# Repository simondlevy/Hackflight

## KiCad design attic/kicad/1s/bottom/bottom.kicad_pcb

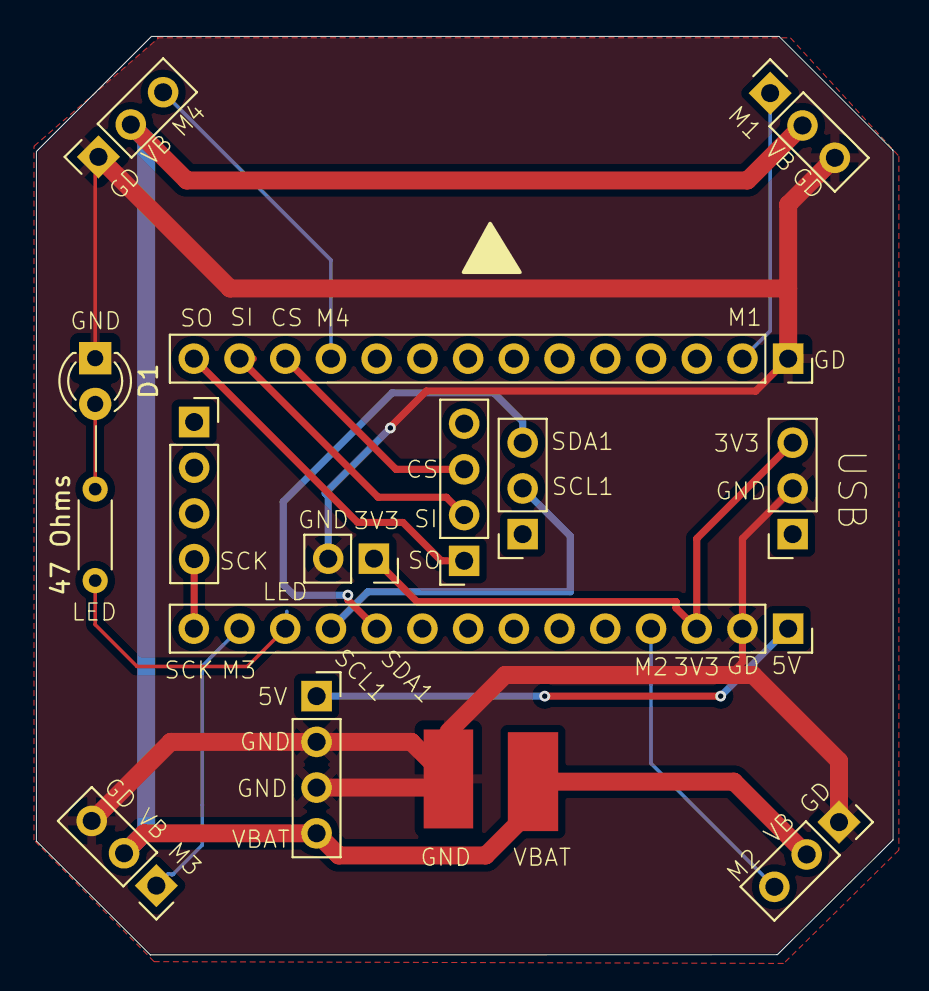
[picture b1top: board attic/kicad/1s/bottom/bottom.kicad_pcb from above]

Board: 2 copper layers, 47.6 x 51.0 mm, 16 parts (0 on the bottom side), 16 nets.

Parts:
D1: LED; LED_D3.0mm
GND_PAD1: Conn_01x01; SolderWirePad_1x01_SMD_5x10mm
J1, J6, J8: Conn_01x04_Socket; PinSocket_1x04_P2.54mm_Vertical
J2, J7: Conn_01x03_Socket; PinSocket_1x03_P2.54mm_Vertical
J3: Conn_01x02_Socket; PinSocket_1x02_P2.54mm_Vertical
J4, J5: Conn_01x14_Socket; PinSocket_1x14_P2.54mm_Vertical
M1, M2, M3, M4: Conn_01x03_Socket; PinSocket_1x03_P2.54mm_Vertical
R1: 47 Ohms; R_Axial_DIN0204_L3.6mm_D1.6mm_P5.08mm_Horizontal
VB_PAD1: Conn_01x01; SolderWirePad_1x01_SMD_5x10mm

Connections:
/3V3: J2.3, J3.1, J4.3
/5V: J4.1, J8.1
/CS: J5.12, J6.3
/GND: D1.1 (K), GND_PAD1.1, J2.2, J3.2, J4.2, J5.1, J8.2, J8.3, M1.3, M2.1, M3.3, M4.1
/LED1: J4.12, R1.2
/M1: J5.2, M1.1
/M2: J4.4, M2.3
/M3: J4.13, M3.1
/M4: J5.11, M4.3
/MISO: J5.14, J6.1
/MOSI: J5.13, J6.2
/SCK: J1.4, J4.14
/SCL1: J4.11, J7.2
/SDA1: J4.10, J7.3
/VBAT: J8.4, M1.2, M2.2, M3.2, M4.2, VB_PAD1.1
unnamed: D1.2 (A), R1.1

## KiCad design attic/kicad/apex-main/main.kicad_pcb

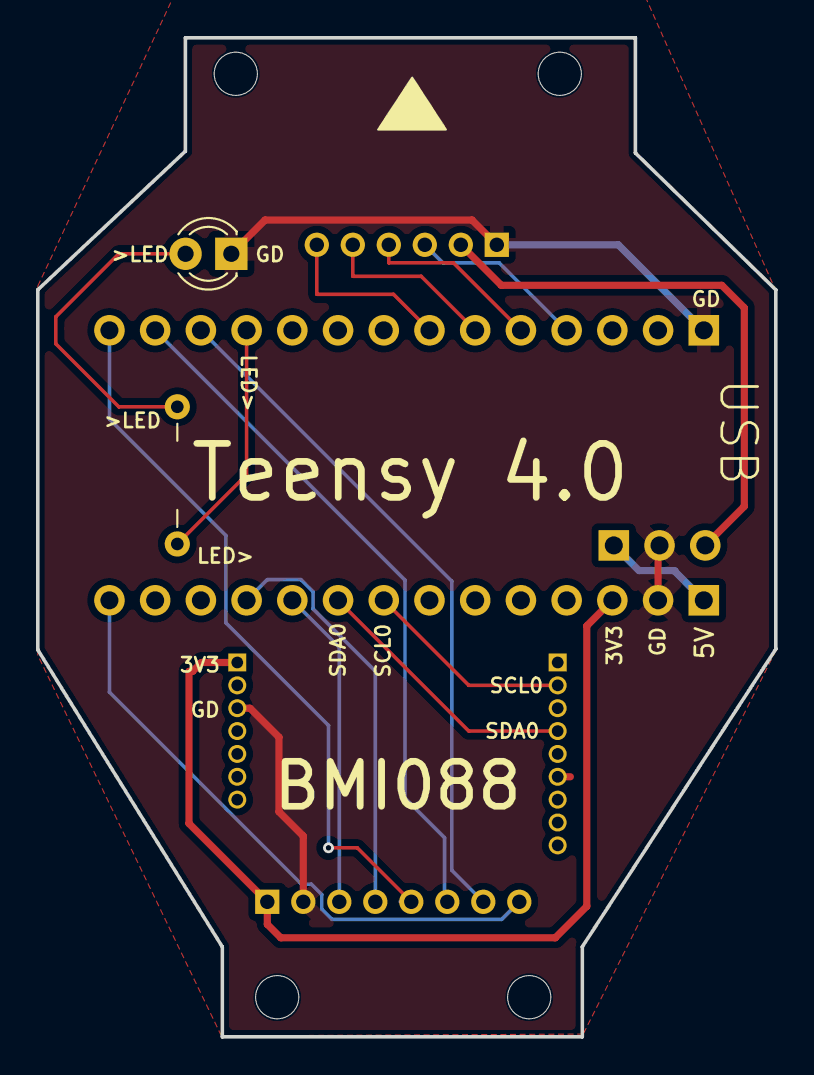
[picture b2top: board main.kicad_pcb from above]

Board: 2 copper layers, 41.0 x 55.5 mm, 16 parts (0 on the bottom side), 18 nets.

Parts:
D1: LED; LED_D3.0mm_FlatTop
H1, H1#2, H1#3, H1#4, H2, H3, H4: MountingHole; MountingHole_2.1mm
J1: Conn_01x14; PinSocket_1x14_P2.54mm_Vertical
J2: Conn_01x14_Socket; PinSocket_1x14_P2.54mm_Vertical
J4: Conn_01x03_Socket; PinHeader_1x03_P2.54mm_Vertical
J5: Conn_01x06; PinSocket_1x06_P2.00mm_Vertical
J6: Conn_01x08; PinSocket_1x08_P2.00mm_Vertical
J7: Conn_01x07; PinHeader_1x07_P1.27mm_Vertical
J8: Conn_01x09; PinHeader_1x09_P1.27mm_Vertical
R1: R; R_Axial_DIN0204_L3.6mm_D1.6mm_P7.62mm_Horizontal

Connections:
/3V3: J2.3, J6.1, J7.1
/5V: J2.1, J4.1
/CS: J1.12, J6.7
/GND: D1.1 (K), J1.1, J2.2, J4.2, J5.1, J6.2, J7.3
/LED: J1.11, R1.2
/M1: J1.4, J5.3
/M2: J1.5, J5.4
/M3: J1.6, J5.5
/M4: J1.7, J5.6
/MISO: J1.14, J6.5
/MOSI: J1.13, J6.6
/SCK: J2.14, J6.8
/SCL0: J2.8, J8.2
/SCL1: J2.11, J6.4
/SDA0: J2.9, J8.4
/SDA1: J2.10, J6.3
/VBAT: J4.3, J5.2
unnamed: D1.2 (A), R1.1

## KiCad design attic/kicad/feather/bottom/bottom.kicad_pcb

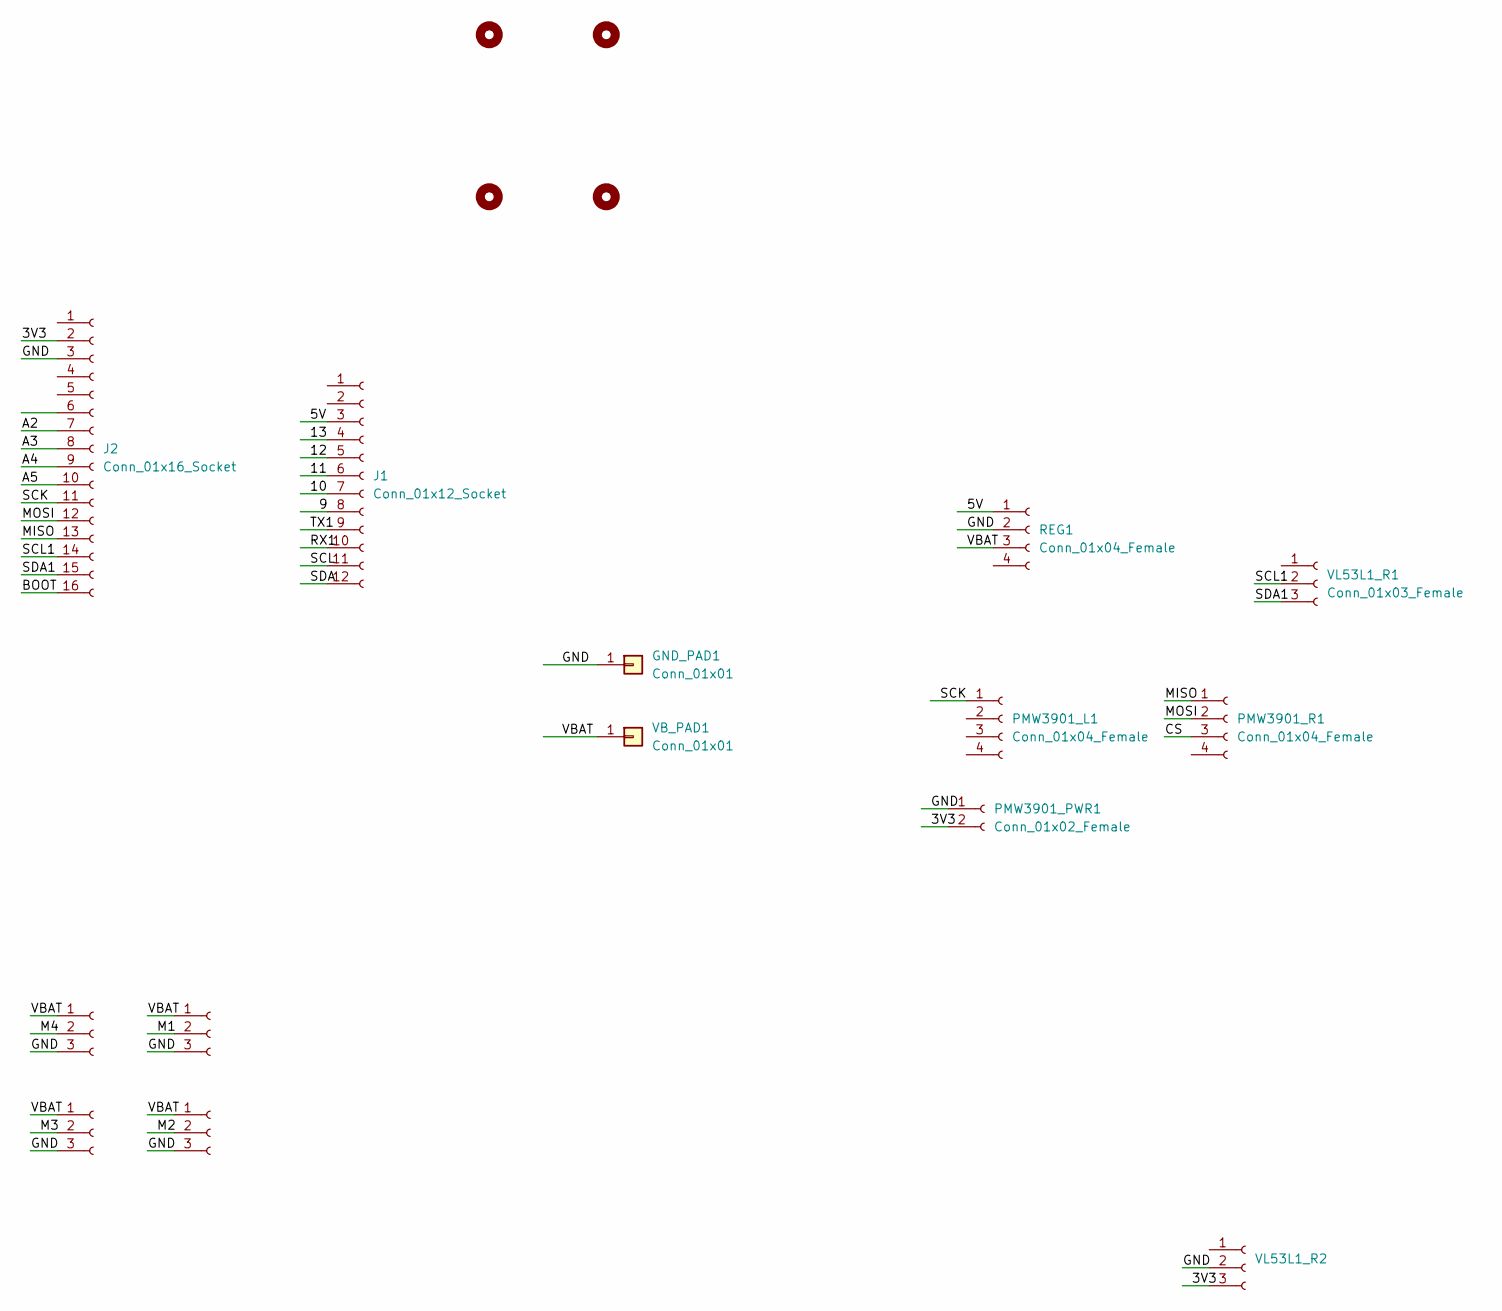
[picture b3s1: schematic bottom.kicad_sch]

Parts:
GND_PAD1: Conn_01x01; SolderWirePad_1x01_SMD_5x10mm
J1: Conn_01x12_Socket; PinSocket_1x14_P2.54mm_Vertical
J2: Conn_01x16_Socket; PinSocket_1x16_P2.54mm_Vertical
M1_GND1: Conn_01x03_Female; PinHeader_1x03_P2.54mm_Vertical
PMW3901_L1, PMW3901_R1: Conn_01x04_Female; PinSocket_1x04_P2.54mm_Vertical
PMW3901_PWR1: Conn_01x02_Female; PinHeader_1x02_P2.54mm_Vertical
POST_1, POST_2, POST_3, POST_4: MountingHole; MountingHole_2.2mm_M2
REG1: Conn_01x04_Female; PinSocket_1x04_P2.54mm_Vertical
VB_PAD1: Conn_01x01; SolderWirePad_1x01_SMD_5x10mm
VL53L1_L3, VL53L1_L4, VL53L1_L5, VL53L1_R1, VL53L1_R2: Conn_01x03_Female; PinHeader_1x03_P2.54mm_Vertical

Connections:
/3V3: J2.2, PMW3901_PWR1.2, VL53L1_R2.3
/5V: J1.3, REG1.1
/9: J1.8
/10: J1.7
/11: J1.6
/12: J1.5
/13: J1.4
/A2: J2.7
/A3: J2.8
/A4: J2.9
/A5: J2.10
/BOOT: J2.16
/CS: PMW3901_R1.3
/GND: GND_PAD1.1, J2.3, M1_GND1.3, PMW3901_PWR1.1, REG1.2, VL53L1_L3.3, VL53L1_L4.3, VL53L1_L5.3, VL53L1_R2.2
/M1: M1_GND1.2
/M2: VL53L1_L3.2
/M3: VL53L1_L5.2
/M4: VL53L1_L4.2
/MISO: J2.13, PMW3901_R1.1
/MOSI: J2.12, PMW3901_R1.2
/RX1: J1.10
/SCK: J2.11, PMW3901_L1.1
/SCL: J1.11
/SCL1: J2.14, VL53L1_R1.2
/SDA: J1.12
/SDA1: J2.15, VL53L1_R1.3
/TX1: J1.9
/VBAT: M1_GND1.1, REG1.3, VB_PAD1.1, VL53L1_L3.1, VL53L1_L4.1, VL53L1_L5.1

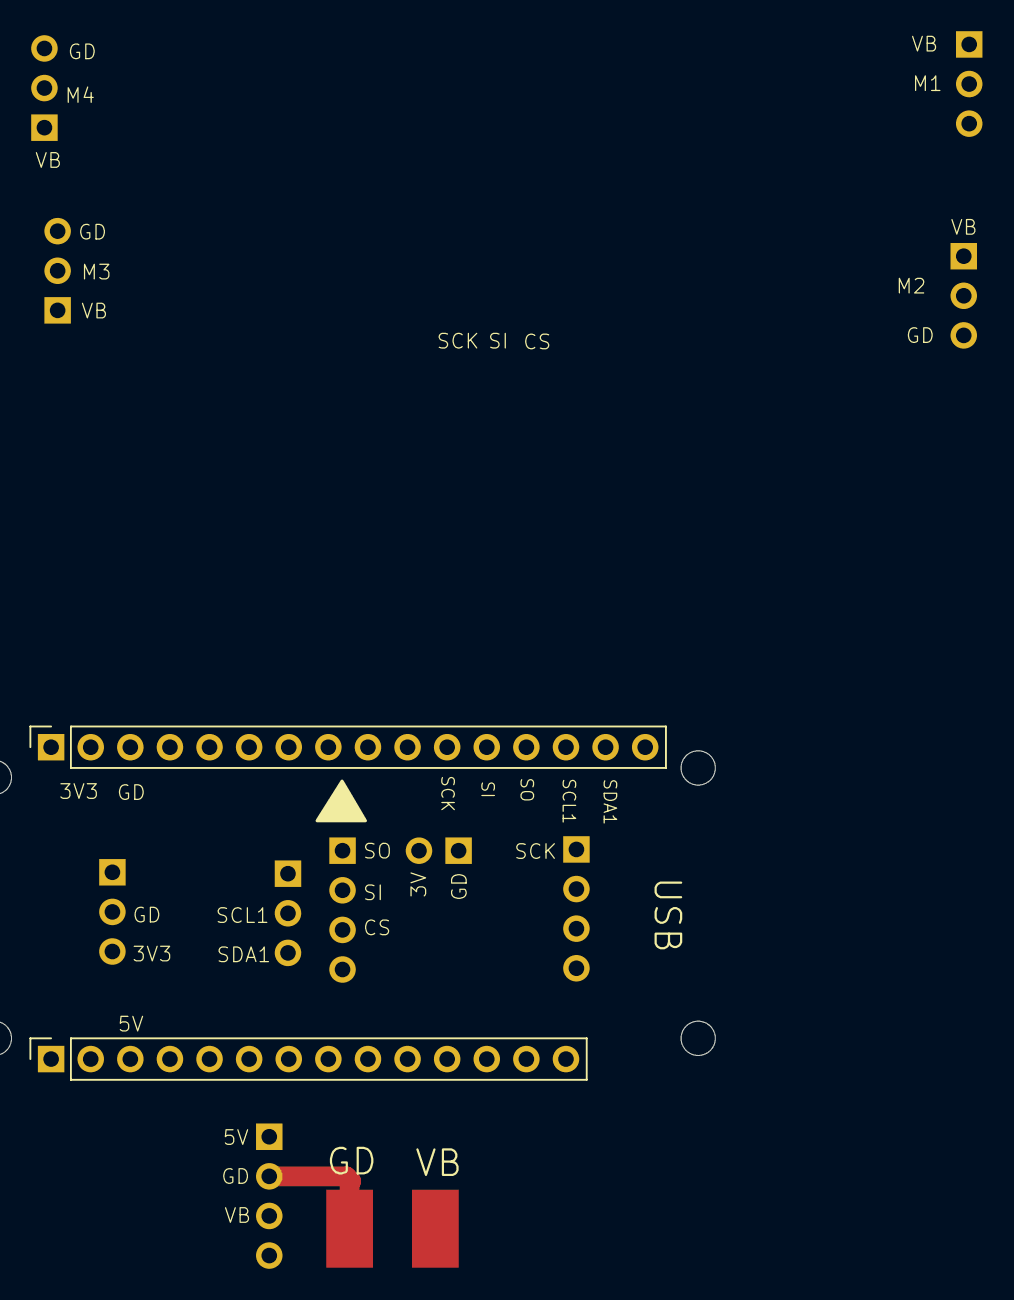
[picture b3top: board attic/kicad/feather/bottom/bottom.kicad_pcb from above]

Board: 2 copper layers, 18 parts (0 on the bottom side), 9 nets.

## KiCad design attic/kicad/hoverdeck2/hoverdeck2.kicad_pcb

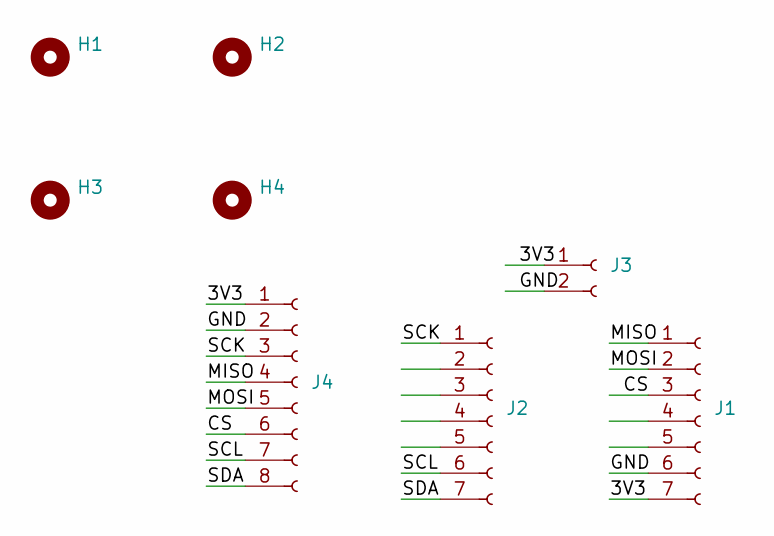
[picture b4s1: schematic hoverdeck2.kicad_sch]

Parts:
H1, H2, H3, H4: MountingHole; MountingHole_2.5mm
J1, J2: Conn_01x07_Socket; PinSocket_1x07_P2.54mm_Vertical
J3: Conn_01x02_Socket; PinSocket_1x02_P2.54mm_Vertical
J4: Conn_01x08_Socket; PinSocket_1x08_P2.00mm_Vertical

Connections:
/3V3: J1.7, J3.1, J4.1
/CS: J1.3, J4.6
/GND: J1.6, J3.2, J4.2
/MISO: J1.1, J4.4
/MOSI: J1.2, J4.5
/SCK: J2.1, J4.3
/SCL: J2.6, J4.7
/SDA: J2.7, J4.8

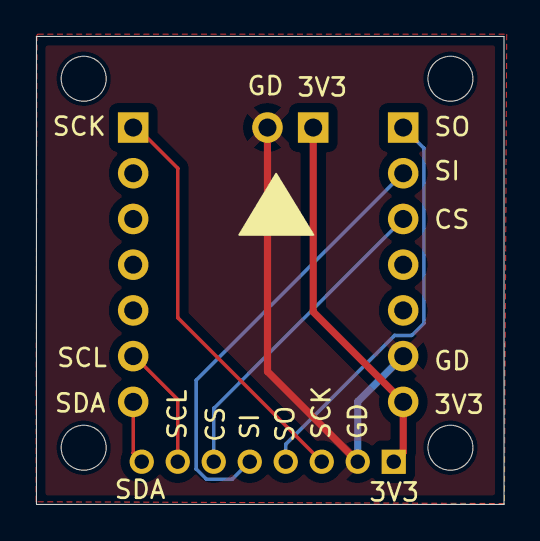
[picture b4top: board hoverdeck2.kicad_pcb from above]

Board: 2 copper layers, 26.0 x 26.0 mm, 8 parts (0 on the bottom side), 8 nets.

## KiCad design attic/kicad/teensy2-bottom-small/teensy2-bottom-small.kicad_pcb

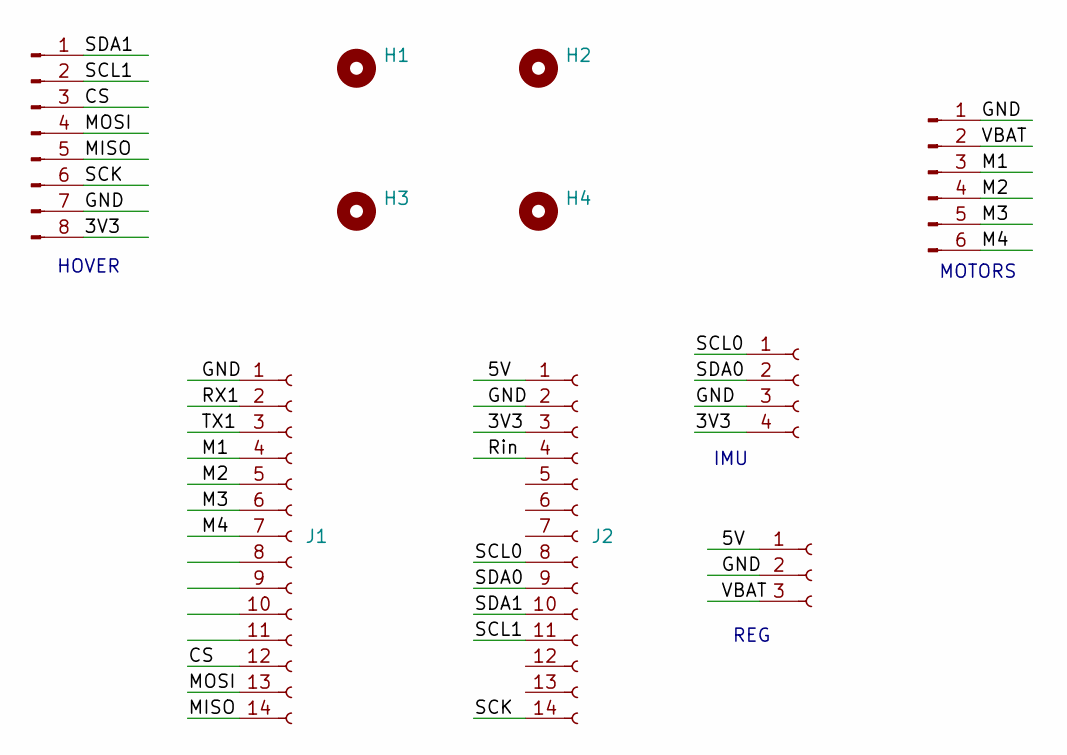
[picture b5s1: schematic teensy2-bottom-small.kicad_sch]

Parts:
H1, H2, H3, H4: MountingHole; MountingHole_2.5mm
J1, J2: Conn_01x14_Socket; PinSocket_1x14_P2.54mm_Vertical
J3: Conn_01x04_Socket; PinHeader_1x04_P2.54mm_Vertical
J4: Conn_01x03_Socket; PinHeader_1x03_P2.54mm_Vertical
J5: Conn_01x06_Pin; PinHeader_1x06_P2.00mm_Vertical
J7: Conn_01x08_Pin; PinSocket_1x08_P2.00mm_Vertical

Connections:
/3V3: J2.3, J3.4, J7.8
/5V: J2.1, J4.1
/CS: J1.12, J7.3
/GND: J1.1, J2.2, J3.3, J4.2, J5.1, J7.7
/M1: J1.4, J5.3
/M2: J1.5, J5.4
/M3: J1.6, J5.5
/M4: J1.7, J5.6
/MISO: J1.14, J7.5
/MOSI: J1.13, J7.4
/RX1: J1.2
/Rin: J2.4
/SCK: J2.14, J7.6
/SCL0: J2.8, J3.1
/SCL1: J2.11, J7.2
/SDA0: J2.9, J3.2
/SDA1: J2.10, J7.1
/TX1: J1.3
/VBAT: J4.3, J5.2

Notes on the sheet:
HOVER
REG
IMU
MOTORS

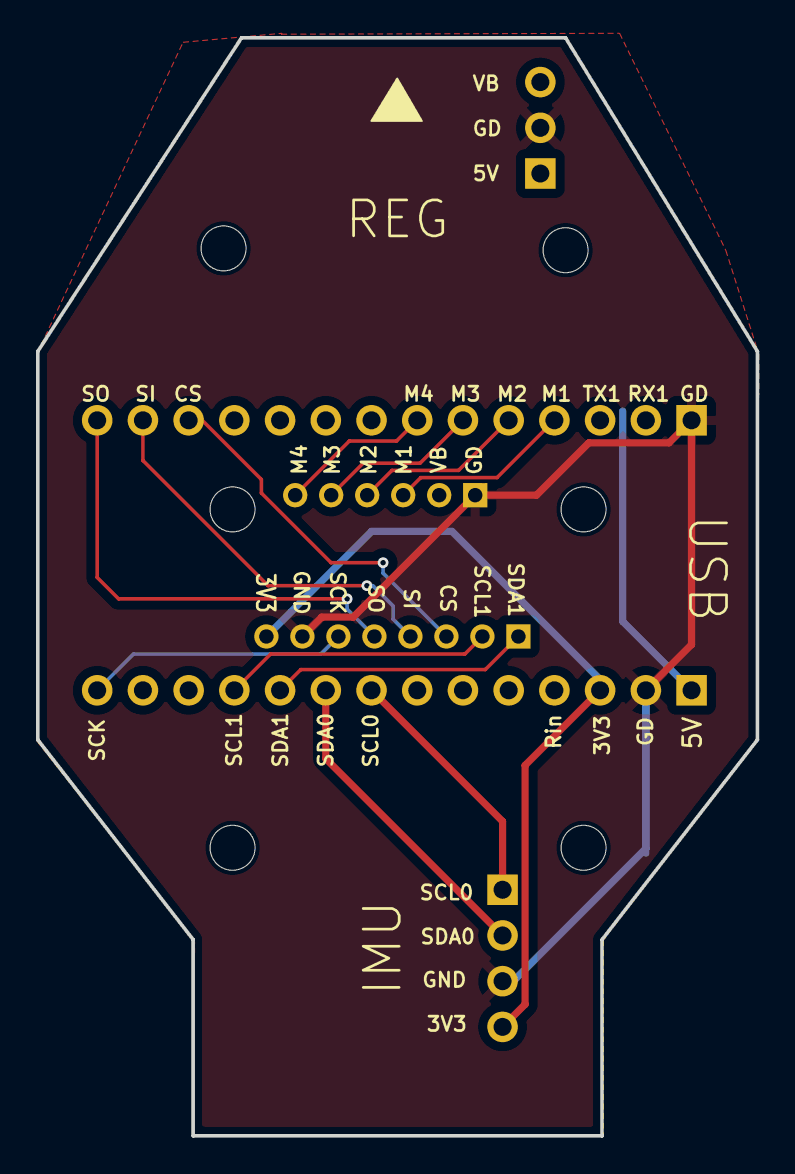
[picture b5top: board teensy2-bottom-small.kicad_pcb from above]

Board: 2 copper layers, 40.0 x 61.0 mm, 10 parts (0 on the bottom side), 16 nets.
